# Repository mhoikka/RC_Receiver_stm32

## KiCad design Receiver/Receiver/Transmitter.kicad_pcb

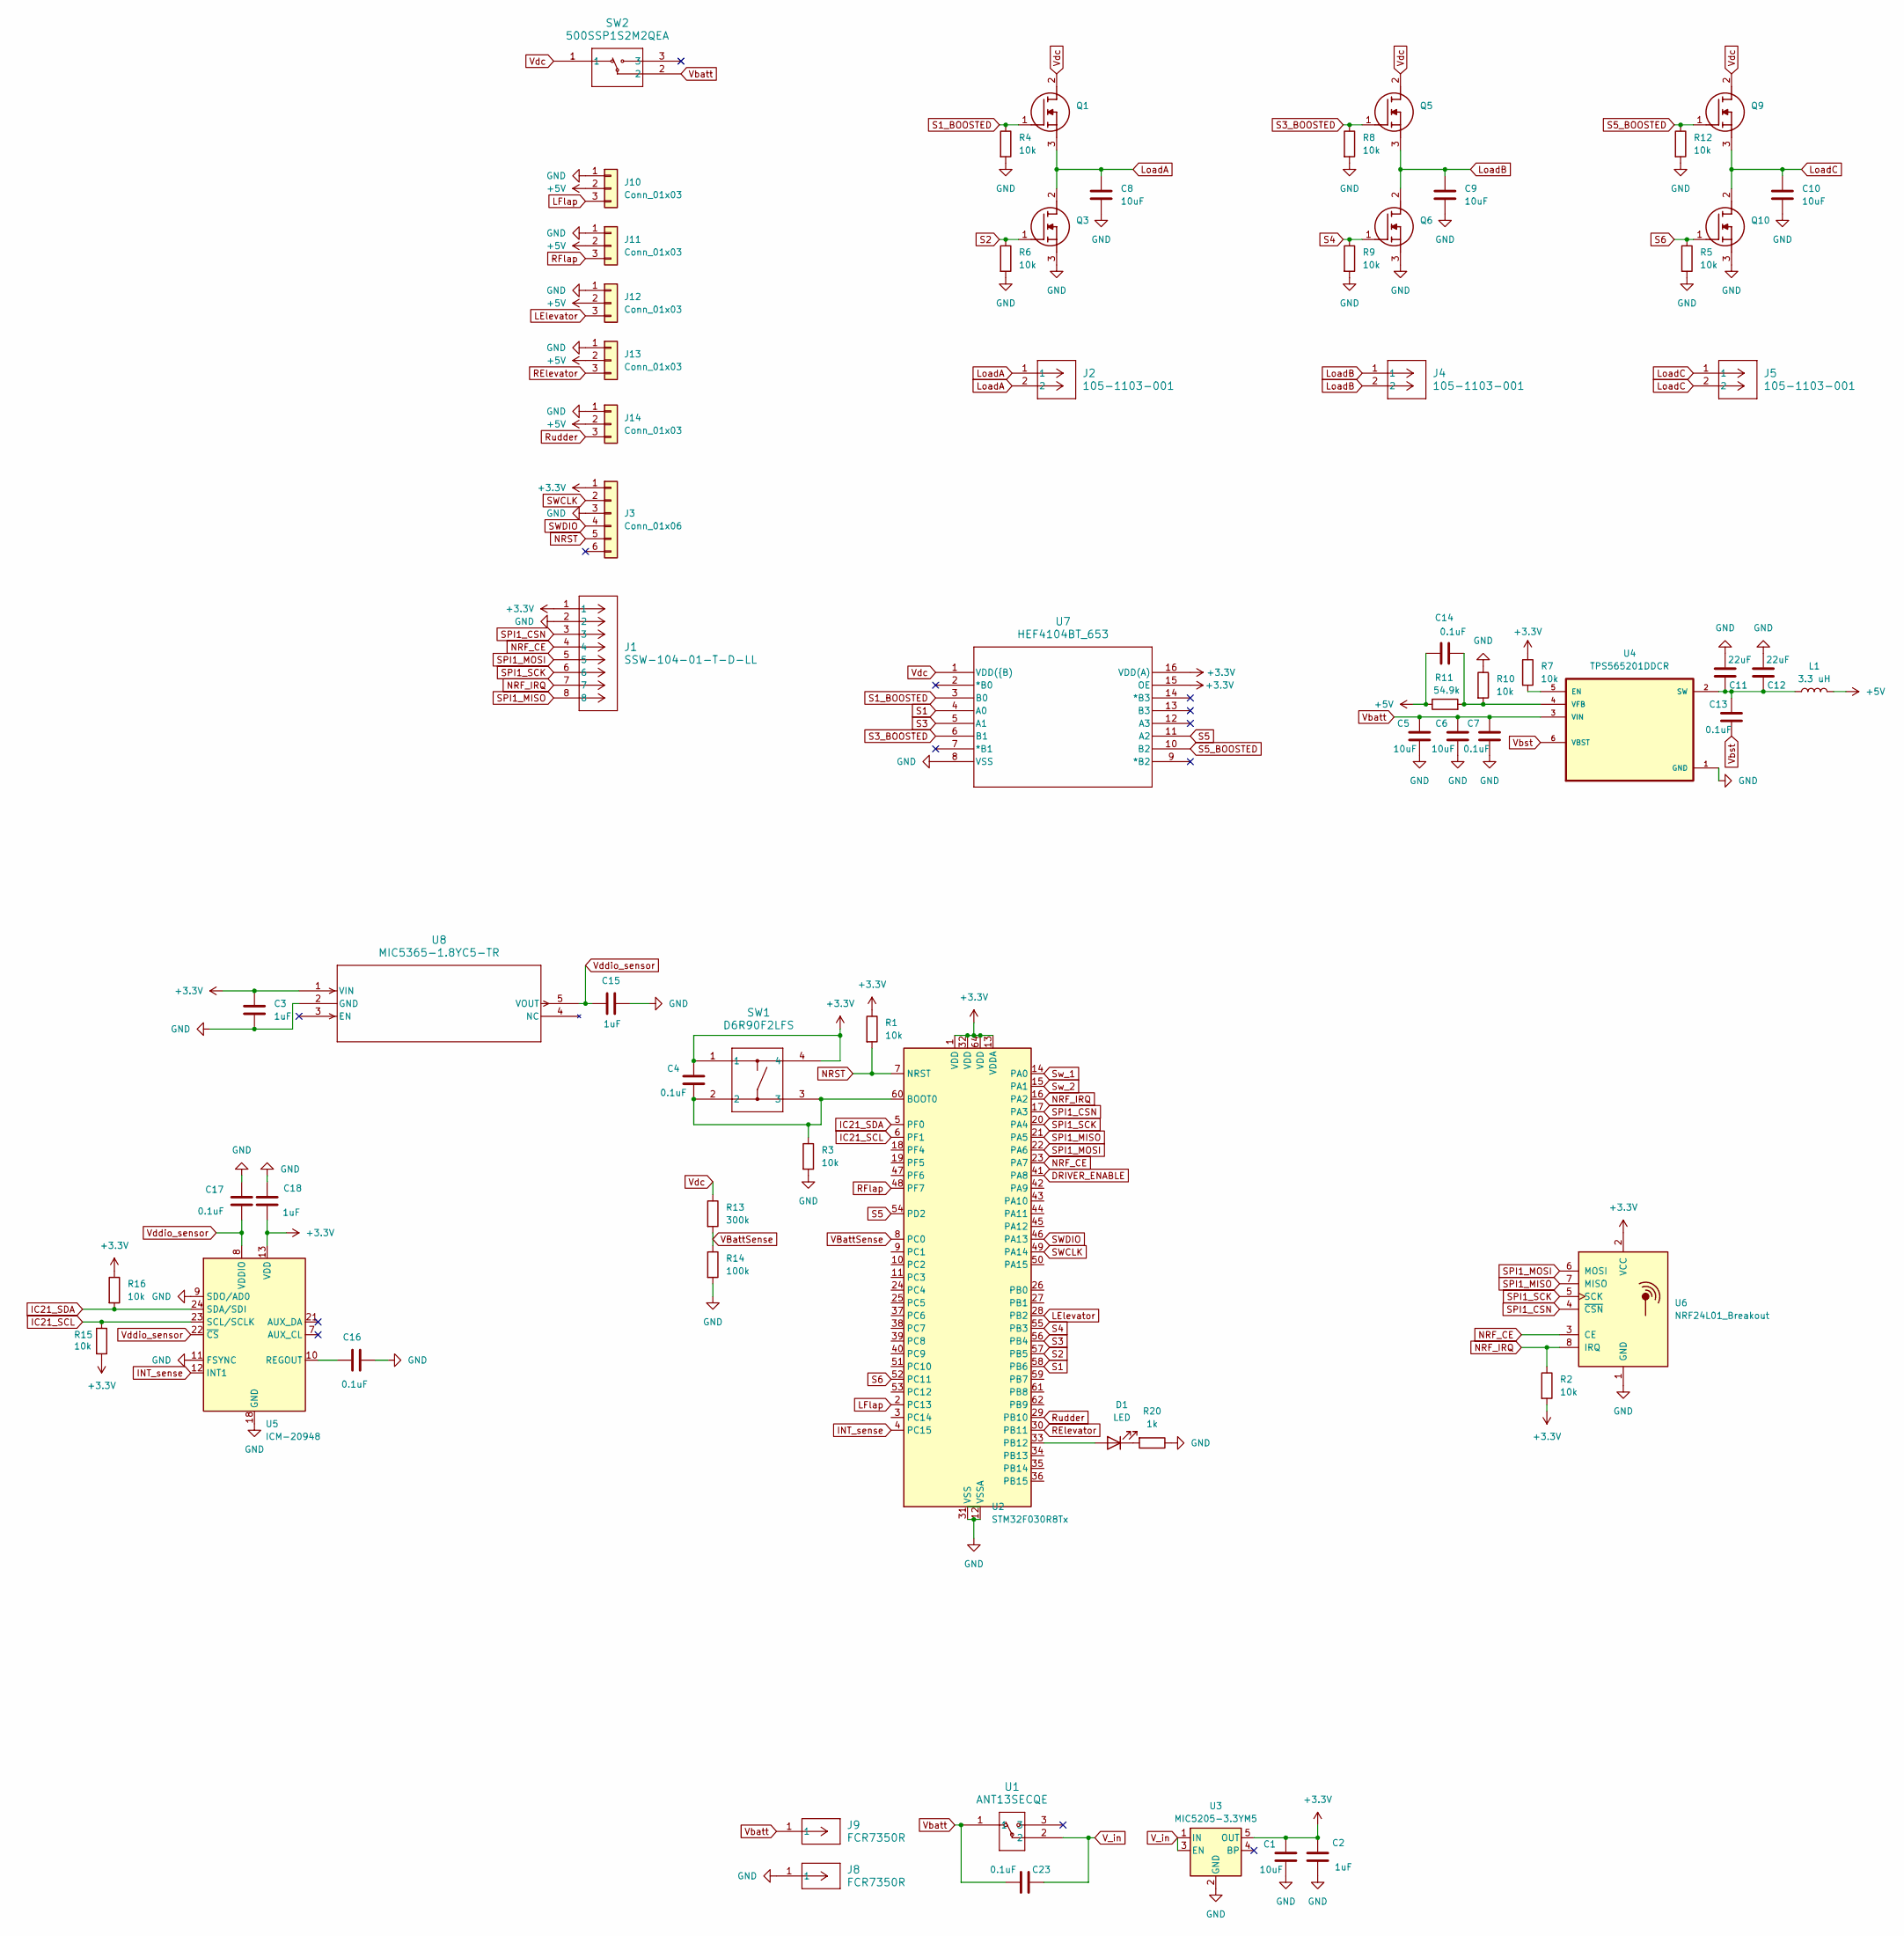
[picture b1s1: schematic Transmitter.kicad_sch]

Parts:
C1, C5, C6, C8, C9, C10: 10uF; C_0603_1608Metric
C2, C3, C15, C18: 1uF; C_0402_1005Metric
C4, C7, C13, C14, C16, C17, C23: 0.1uF; C_0402_1005Metric
C11, C12: 22uF; C_0603_1608Metric
D1: LED; D_0603_1608Metric
J1: SSW-104-01-T-D-LL; CON8_2X4_TU_SSQ
J2, J4, J5: 105-1103-001; CONN_105-1102-001
J3: Conn_01x06; PinHeader_1x06_P2.54mm_Vertical
J8, J9: FCR7350R; CONN1_FCR7350R_CLF
J10, J11, J12, J13, J14: Conn_01x03; PinHeader_1x03_P2.54mm_Vertical
L1: 3.3 uH; 3.3uH
Q1, Q3, Q5, Q6, Q9, Q10: RJF0408JPD-01#J3; RJF0408JPD01J3; Manufacturer_Part_Number RJF0408JPD-01#J3
R1, R2, R3, R4, R5, R6, R7, R8, R9, R10, R12, R15, R16: 10k; R_0402_1005Metric
R11: 54.9k; R_1206_3216Metric
R13: 300k; R_0603_1608Metric
R14: 100k; R_0603_1608Metric
R20: 1k; D_0603_1608Metric
SW1: D6R90F2LFS; D6R90_CNK
SW2: 500SSP1S2M2QEA; 500SSP1_EWI
U1: ANT13SECQE; ANT13SEC_CRS
U2: STM32F030R8Tx; LQFP-64_10x10mm_P0.5mm
U3: MIC5205-3.3YM5; SOT-23-5
U4: TPS565201DDCR; ServoVoltageRegulator
U5: ICM-20948; InvenSense_QFN-24_3x3mm_P0.4mm
U6: NRF24L01_Breakout; nRF24L01_Breakout
U7: HEF4104BT_653; SO16_SOT109-1_NEX
U8: MIC5365-1.8YC5-TR; SC-70_C5_MCH

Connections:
+3.3V: C1.1, C2.1, C3.1, C4.2, C18.1, J1.1, J3.1, R1.1, R2.2, R7.1, R15.2, R16.1, SW1.1, SW1.4, U2.1 (VDD), U2.13 (VDDA), U2.32 (VDD), U2.64 (VDD), U3.5 (OUT), U5.13 (VDD), U6.2 (VCC), U7.15 (OE), U7.16 (VDD(A)), U8.1 (VIN)
+5V: C14.1, J10.2, J11.2, J12.2, J13.2, J14.2, L1.2, R11.1
DRIVER_ENABLE: U2.41 (PA8)
GND: C1.2, C2.2, C3.2, C5.2, C6.2, C7.2, C8.2, C9.2, C10.2, C11.2, C12.2, C15.2, C16.2, C17.1, C18.2, J1.2, J3.3, J8.1, J10.1, J11.1, J12.1, J13.1, J14.1, Q3.3 (S), Q6.3 (S), Q10.3 (S), R3.2, R4.2, R5.2, R6.2, R8.2, R9.2, R10.1, R12.2, R14.2, R20.1, U2.12 (VSSA), U2.31 (VSS), U2.63 (VSS), U3.2 (GND), U4.1 (GND), U5.9 (SDO/AD0), U5.11 (FSYNC), U5.18 (GND), U5.20 (GND), U6.1 (GND), U7.8 (VSS), U8.2 (GND)
IC21_SCL: R15.1, U2.6 (PF1), U5.23 (SCL/SCLK)
IC21_SDA: R16.2, U2.5 (PF0), U5.24 (SDA/SDI)
INT_sense: U2.4 (PC15), U5.12 (INT1)
LElevator: J12.3, U2.28 (PB2)
LFlap: J10.3, U2.2 (PC13)
LoadA: C8.1, J2.1, J2.2, Q1.3 (S), Q3.2 (D)
LoadB: C9.1, J4.1, J4.2, Q5.3 (S), Q6.2 (D)
LoadC: C10.1, J5.1, J5.2, Q9.3 (S), Q10.2 (D)
NRF_CE: J1.4, U2.23 (PA7), U6.3 (CE)
NRF_IRQ: J1.7, R2.1, U2.16 (PA2), U6.8 (IRQ)
NRST: J3.5, R1.2, U2.7 (NRST)
unnamed: D1.2 (A), U2.33 (PB12)
unnamed: D1.1 (K), R20.2
unnamed: C4.1, R3.1, SW1.2, SW1.3, U2.60 (BOOT0)
unnamed: R7.2, U4.5 (EN)
unnamed: C11.1, C12.1, C13.1, L1.1, U4.2 (SW)
unnamed: C14.2, R10.2, R11.2, U4.4 (VFB)
unnamed: C16.1, U5.10 (REGOUT)
RElevator: J13.3, U2.30 (PB11)
RFlap: J11.3, U2.48 (PF7)
Rudder: J14.3, U2.29 (PB10)
S1: U2.58 (PB6), U7.4 (A0)
S1_BOOSTED: Q1.1 (G), R4.1, U7.3 (B0)
S2: Q3.1 (G), R6.1, U2.57 (PB5)
S3: U2.56 (PB4), U7.5 (A1)
S3_BOOSTED: Q5.1 (G), R8.1, U7.6 (B1)
S4: Q6.1 (G), R9.1, U2.55 (PB3)
S5: U2.54 (PD2), U7.11 (A2)
S5_BOOSTED: Q9.1 (G), R12.1, U7.10 (B2)
S6: Q10.1 (G), R5.1, U2.52 (PC11)
SPI1_CSN: J1.3, U2.17 (PA3), U6.4 (~CSN)
SPI1_MISO: J1.8, U2.21 (PA5), U6.7 (MISO)
SPI1_MOSI: J1.5, U2.22 (PA6), U6.6 (MOSI)
SPI1_SCK: J1.6, U2.20 (PA4), U6.5 (SCK)
SWCLK: J3.2, U2.49 (PA14)
SWDIO: J3.4, U2.46 (PA13)
Sw_1: U2.14 (PA0)
Sw_2: U2.15 (PA1)
VBattSense: R13.2, R14.1, U2.8 (PC0)
V_in: C23.2, U1.2, U3.1 (IN), U3.3 (EN)
Vbatt: C5.1, C6.1, C7.1, C23.1, J9.1, SW2.2, U1.1, U4.3 (VIN)
Vbst: C13.2, U4.6 (VBST)
Vdc: Q1.2 (D), Q5.2 (D), Q9.2 (D), R13.1, SW2.1, U7.1 (VDD({B))
Vddio_sensor: C15.1, C17.2, U5.8 (VDDIO), U5.22 (~CS), U8.5 (VOUT)

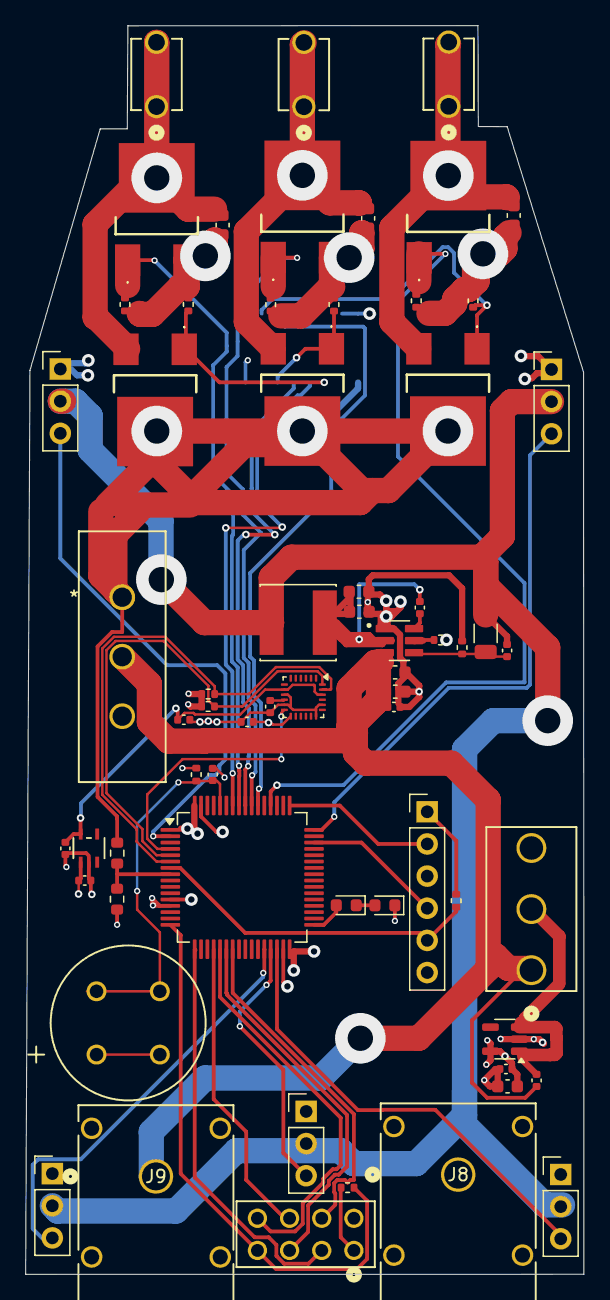
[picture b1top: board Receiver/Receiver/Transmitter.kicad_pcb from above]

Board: 4 copper layers, 44.1 x 98.6 mm, 65 parts (1 on the bottom side), 45 nets.

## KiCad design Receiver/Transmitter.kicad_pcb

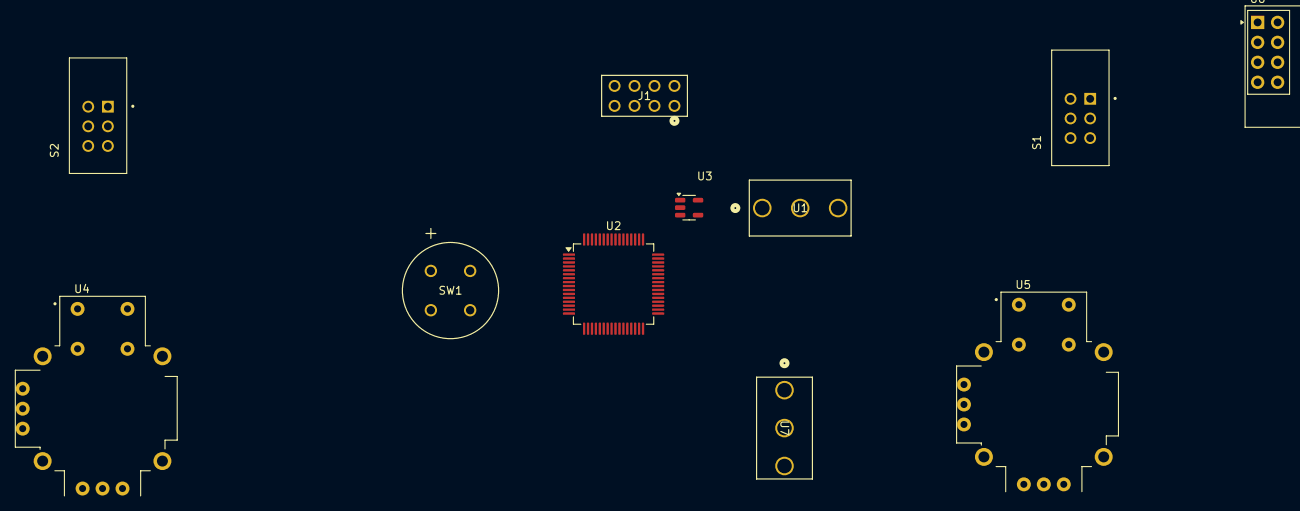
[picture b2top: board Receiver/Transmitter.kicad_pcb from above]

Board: 2 copper layers, 11 parts (0 on the bottom side), 18 nets, no tracks yet.

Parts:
J1: SSW-104-01-T-D-LL; CON8_2X4_TU_SSQ
S1, S2: PBH2UOANAGX; SW_PBH2UOANAGX
SW1: D6R90F2LFS; D6R90_CNK
U1, U7: ANT13SECQE; ANT13SEC_CRS
U2: STM32F030R8Tx; LQFP-64_10x10mm_P0.5mm
U3: MIC5205-3.3YM5; SOT-23-5
U4, U5: COM-09032; XDCR_COM-09032
U6: NRF24L01_Breakout; nRF24L01_Breakout

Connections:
+3.3V: J1.2, S1.3, S1.6, SW1.1, SW1.4, U3.5 (OUT), U4.H1 (H+), U4.V1 (V+), U5.H1 (H+), U5.V1 (V+), U6.2 (VCC), U7.2
GND: J1.1, S1.1, S1.4, U2.12 (VSSA), U2.31 (VSS), U2.63 (VSS), U3.2 (GND), U4.B2A (SEL-), U4.H3 (H-), U4.V3 (V-), U5.B2A (SEL-), U5.H3 (H-), U5.V3 (V-), U6.1 (GND), U7.3
H_Joystick1: U2.43 (PA10), U4.H2 (H)
H_Joystick2: U2.50 (PA15), U5.H2 (H)
NRF_CE: J1.3, U6.3 (CE)
NRF_IRQ: J1.8, U6.8 (IRQ)
unnamed: SW1.2, SW1.3, U2.60 (BOOT0)
SEL_Joystick1: U2.44 (PA11), U4.B1A (SEL+)
SEL_Joystick2: U2.26 (PB0), U5.B1A (SEL+)
SPI1_CSN: J1.4, U2.20 (PA4), U6.4 (~CSN)
SPI1_MISO: J1.7, U2.22 (PA6), U6.7 (MISO)
SPI1_MOSI: J1.6, U2.23 (PA7), U6.6 (MOSI)
SPI1_SCK: J1.5, U2.21 (PA5), U6.5 (SCK)
Sw_1: U2.15 (PA1), U7.1
Sw_2: S1.2, S1.5, U2.16 (PA2)
V_Joystick1: U2.42 (PA9), U4.V2 (V)
V_Joystick2: U2.45 (PA12), U5.V2 (V)
V_in: U1.2, U3.1 (IN), U3.3 (EN)

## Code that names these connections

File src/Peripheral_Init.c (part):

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  GPIO_SetBits(GPIOB, GPIO_Pin_12); // Turn on test diode to confirm setup function worked
  uint32_t time_on = 0;
  for(int i = 0; i < 100; i++){ // TODO test how fast loaded arm moves, unloaded arm is rated to move at 0.09 s + 0.01 s/60 degrees at 4.8 V so I gave it 150 ms here
    GPIO_SetBits(GPIOC, GPIO_Pin_13); // LFlap // Servo uses PWM to control angle of arm
    GPIO_SetBits(GPIOF, GPIO_Pin_7); // Rflap
    GPIO_SetBits(GPIOB, GPIO_Pin_2); // Lelevator
    GPIO_SetBits(GPIOB, GPIO_Pin_11); // Relevator
    GPIO_SetBits(GPIOB, GPIO_Pin_10); // Rudder
    
    time_on = 800 + angle * 500; // in microseconds
    delay_microseconds(time_on, NULL); // exceeds 1000 or 1500 ms (45-90 degree angle for servo arm) as specified to ensure motor operates
    GPIO_ResetBits(GPIOC, GPIO_Pin_13); // LFlap 
    GPIO_ResetBits(GPIOF, GPIO_Pin_7); // Rflap
    GPIO_ResetBits(GPIOB, GPIO_Pin_2); // Lelevator
    GPIO_ResetBits(GPIOB, GPIO_Pin_11); // Relevator
    GPIO_ResetBits(GPIOB, GPIO_Pin_10); // Rudder
    delay_microseconds(20000 - time_on, NULL);
  }  
  for(int i = 0; i < 100; i++){ // TODO test how fast loaded arm moves, unloaded arm is rated to move at 0.09 s + 0.01 s/60 degrees at 4.8 V so I gave it 150 ms here
    GPIO_SetBits(GPIOC, GPIO_Pin_13); // LFlap // Servo uses PWM to control angle of arm
    GPIO_SetBits(GPIOF, GPIO_Pin_7); // Rflap
    GPIO_SetBits(GPIOB, GPIO_Pin_2); // Lelevator
    GPIO_SetBits(GPIOB, GPIO_Pin_11); // Relevator
    GPIO_SetBits(GPIOB, GPIO_Pin_10); // Rudder
    
    time_on = 800 + 0 * 500; // in microseconds
    delay_microseconds(time_on, NULL); // exceeds 1000 or 1500 ms (45-90 degree angle for servo arm) as specified to ensure motor operates
    GPIO_ResetBits(GPIOC, GPIO_Pin_13); // LFlap 
    GPIO_ResetBits(GPIOF, GPIO_Pin_7); // Rflap
    GPIO_ResetBits(GPIOB, GPIO_Pin_2); // Lelevator
    GPIO_ResetBits(GPIOB, GPIO_Pin_11); // Relevator
    GPIO_ResetBits(GPIOB, GPIO_Pin_10); // Rudder
    delay_microseconds(20000 - time_on, NULL);
  } 
}
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  GPIO_InitTypeDef GPIO_InitStruct;
  RCC_AHBPeriphClockCmd(RCC_AHBPeriph_GPIOC, ENABLE); // enable clocks for GPIO peripheral 
  RCC_APB2PeriphClockCmd(RCC_APB2Periph_ADC1, ENABLE); // enable clocks for ADC peripheral
  // Configure PC0 as analog input for battery voltage measurement
  GPIO_InitStruct.GPIO_Pin = GPIO_Pin_0;
  GPIO_InitStruct.GPIO_Mode = GPIO_Mode_AN;
  GPIO_InitStruct.GPIO_Speed = GPIO_Speed_50MHz;
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  //RCC_APB2PeriphClockCmd(RCC_APB2Periph_SYSCFG, ENABLE);//
  RCC_AHBPeriphClockCmd(RCC_AHBPeriph_GPIOB, ENABLE);
  
  // Use pins PF0 and PF1 for I2C (STM32F030R8T6)
  GPIO_InitTypeDef GPIO_InitStruct;
  GPIO_PinAFConfig(GPIOF, GPIO_PinSource0, GPIO_AF_1);
  GPIO_PinAFConfig(GPIOF, GPIO_PinSource1, GPIO_AF_1);
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
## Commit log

2025-08-19 V1 Receiver PCB with inverter prototype
2025-10-17 Updated KICAD files for V1, corrected SWDIO header
2025-10-17 Working Servo motor test and 3-phase AC test
2025-10-22 PCB V2 updates
2025-10-26 Removed extra voltage converter and rerouted PCB
2025-10-26 Added battery voltage sensing hardware to PCB
2025-10-31 V2 PCB
2025-11-05 Minor KiCAD changes
2025-12-13 Fixed HBridge clock issue and added servo testing cycle on reboot
2025-12-27 Fixed Rflap servo code
